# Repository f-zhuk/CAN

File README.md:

# CAN
## General description
The work is in progress and is currently not ready for real-life application.  
This repository contains hardware, firmware, and software dedicated to the creation of custom CANopen systems for vehicles.  
Such custom systems could fit old cars with heavily damaged harnesses and vehicles that do not have electronic equipment by default, for example, boats, kayaks, and bicycles.
## Hardware
The complete system should consist of multiple functional blocks. Blocks should be as cheap and simple as possible while implementing complete functions like combination switch assembly, left tail light assembly, and door controls.  
Each functional block should be designed around a unified MCU module and simple interconnection boards to adapt signals from the MCU module to the systems of the block.  
Interconnection boards may provide 24LC I2C EEPROM memory for identification and non-volatile parameter storage.  
### MCU
MCU module should be self-sufficient and electrically ready for insertion in the CAN bus system. To achieve this, the MCU module has a power supply converter and CAN driver aside from the controller.  
For the first prototype, the PIC18 family was selected. PIC18F83K26 has a built-in CAN periphery and a reasonable price.  
MCU module has +12V power input, +5V power input/output, CAN, UART, 8xGPIO(PC7:PC0)  
### USB-UART
Most important interconnection board. It provides a USB to UART bridge to provide a simple debug interface.  
USB-UART board is built with MCP2200. It is connected not only through UART but also 5xGPIO. Additionally, 24LC16 I2C EEPROM memory is connected to C6 and C7. C5 is connected to the bus termination control.  
## Firmware
Heavily updated code described in AN945. The application note code was written for an older MCU. PIC18F83K26AN945 is not supported by the compiler the code was written for and the code is not compatible with the new compiler.  
AN945 default config:  
ADC is on (probably unused)  
PORT D is all output (probably unused)  
PORT B pin 5 is bit 0 of TPDO1, pin 4 is bit 1  
State of PORTB pins 4 and 5 compared to their states on previous DemoProcessEvents() call, change, rise and fall events detected and distinguished, written to OD  
Dictionary object 0x6005subondex 1 (uIOinIntEnable) bits 0 and 1  
Async transmission for TPDO1 by default  
PDO transmission type could be changed by writing to TPDO1 subindex 2  
## Software
The software is written in Python.

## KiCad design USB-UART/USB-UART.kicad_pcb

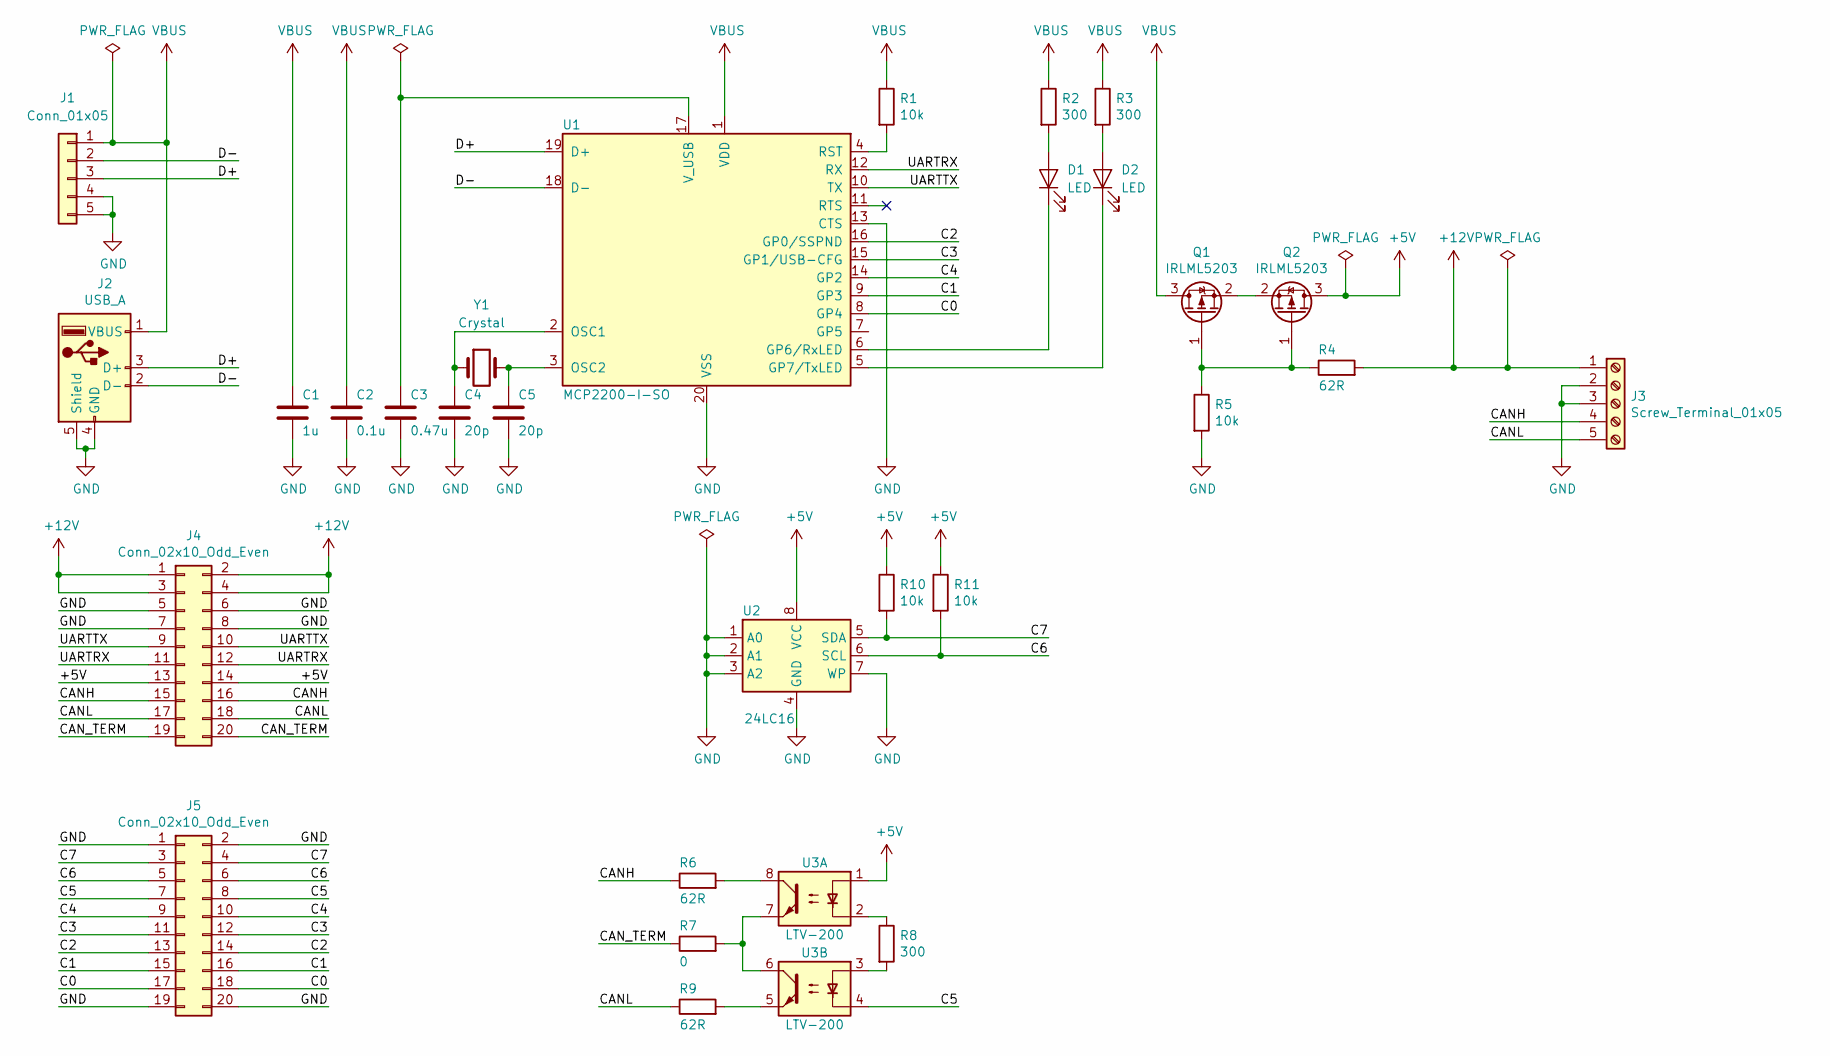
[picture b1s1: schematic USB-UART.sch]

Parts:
C1: 1u; C_0603_1608Metric
C2: 0.1u; C_0603_1608Metric
C3: 0.47u; C_0603_1608Metric
C4, C5: 20p; C_0603_1608Metric
D1, D2: LED; LED_0603_1608Metric
J1: Conn_01x05; PinHeader_1x05_P2.54mm_Vertical
J2: USB_A; USB_A_Integrated
J3: Screw_Terminal_01x05; TerminalBlock_bornier-5_P5.08mm
J4, J5: Conn_02x10_Odd_Even; PinSocket_2x10_P2.54mm_Vertical
Q1, Q2: IRLML5203; SOT-23
R1, R5, R10, R11: 10k; R_0603_1608Metric
R2, R3, R8: 300; R_0603_1608Metric
R4, R6, R9: 62R; R_0603_1608Metric
R7: 0; R_0603_1608Metric
U1: MCP2200-I-SO; SOIC-20W_7.5x12.8mm_P1.27mm
U2: 24LC16; SOIC-8_3.9x4.9mm_P1.27mm
U3: LTV-200; SOIC-8_3.9x4.9mm_P1.27mm
Y1: Crystal; Crystal_HC49-U_Vertical

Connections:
+5V: J4.13, J4.14, Q2.3 (D), R10.1, R11.1, U2.8 (VCC), U3.1
+12V: J3.1, J4.1, J4.2, J4.3, J4.4, R4.2
/C0: J5.17, J5.18, U1.8 (GP4)
/C1: J5.15, J5.16, U1.9 (GP3)
/C2: J5.13, J5.14, U1.16 (GP0/SSPND)
/C3: J5.11, J5.12, U1.15 (GP1/USB-CFG)
/C4: J5.9, J5.10, U1.14 (GP2)
/C5: J5.7, J5.8, U3.4
/C6: J5.5, J5.6, R11.2, U2.6 (SCL)
/C7: J5.3, J5.4, R10.2, U2.5 (SDA)
/CANH: J3.4, J4.15, J4.16, R6.1
/CANL: J3.5, J4.17, J4.18, R9.1
/CAN_TERM: J4.19, J4.20, R7.1
/D+: J1.3, J2.3 (D+), U1.19 (D+)
/D-: J1.2, J2.2 (D-), U1.18 (D-)
/UARTRX: J4.11, J4.12, U1.12 (RX)
/UARTTX: J4.9, J4.10, U1.10 (TX)
GND: C1.2, C2.2, C3.2, C4.2, C5.2, J1.4, J1.5, J2.4 (GND), J2.5 (Shield), J3.2, J3.3, J4.5, J4.6, J4.7, J4.8, J5.1, J5.2, J5.19, J5.20, R5.2, U1.13 (CTS), U1.20 (VSS), U2.1 (A0), U2.2 (A1), U2.3 (A2), U2.4 (GND), U2.7 (WP)
unnamed: C3.1, U1.17 (V_USB)
unnamed: C4.1, U1.2 (OSC1), Y1.1
unnamed: C5.1, U1.3 (OSC2), Y1.2
unnamed: D1.1 (K), U1.6 (GP6/RxLED)
unnamed: D1.2 (A), R2.2
unnamed: D2.1 (K), U1.5 (GP7/TxLED)
unnamed: D2.2 (A), R3.2
unnamed: Q1.1 (G), Q2.1 (G), R4.1, R5.1
unnamed: Q1.2 (S), Q2.2 (S)
unnamed: R1.2, U1.4 (RST)
unnamed: R6.2, U3.8
unnamed: R7.2, U3.6, U3.7
unnamed: R8.1, U3.2
unnamed: R8.2, U3.3
unnamed: R9.2, U3.5
VBUS: C1.1, C2.1, J1.1, J2.1 (VBUS), Q1.3 (D), R1.1, R2.1, R3.1, U1.1 (VDD)

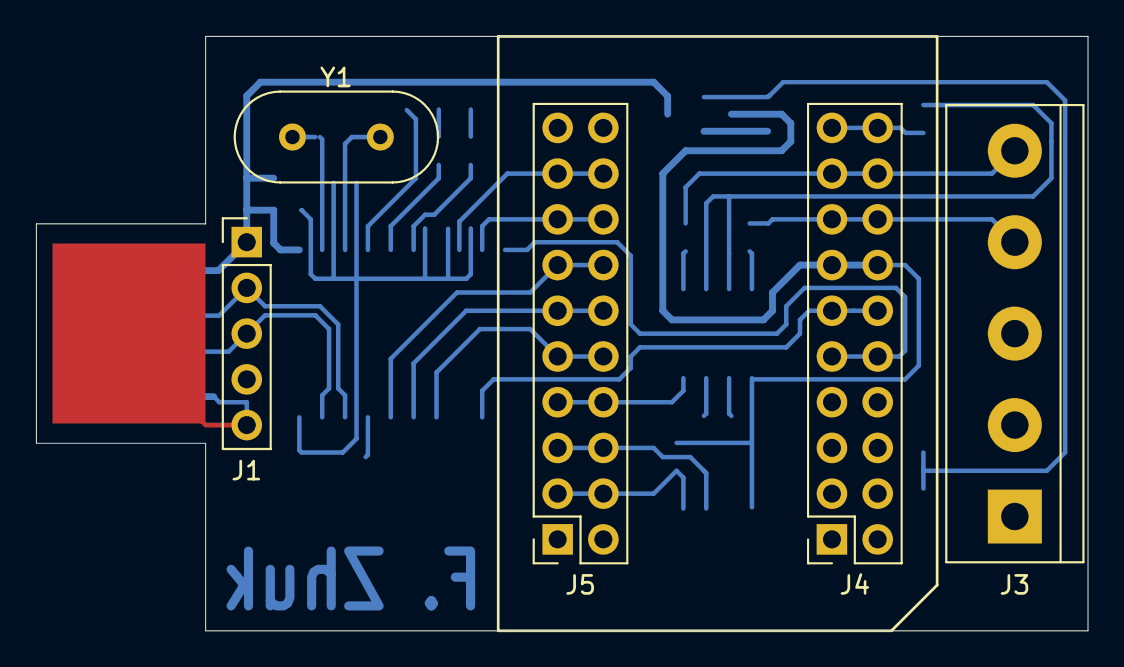
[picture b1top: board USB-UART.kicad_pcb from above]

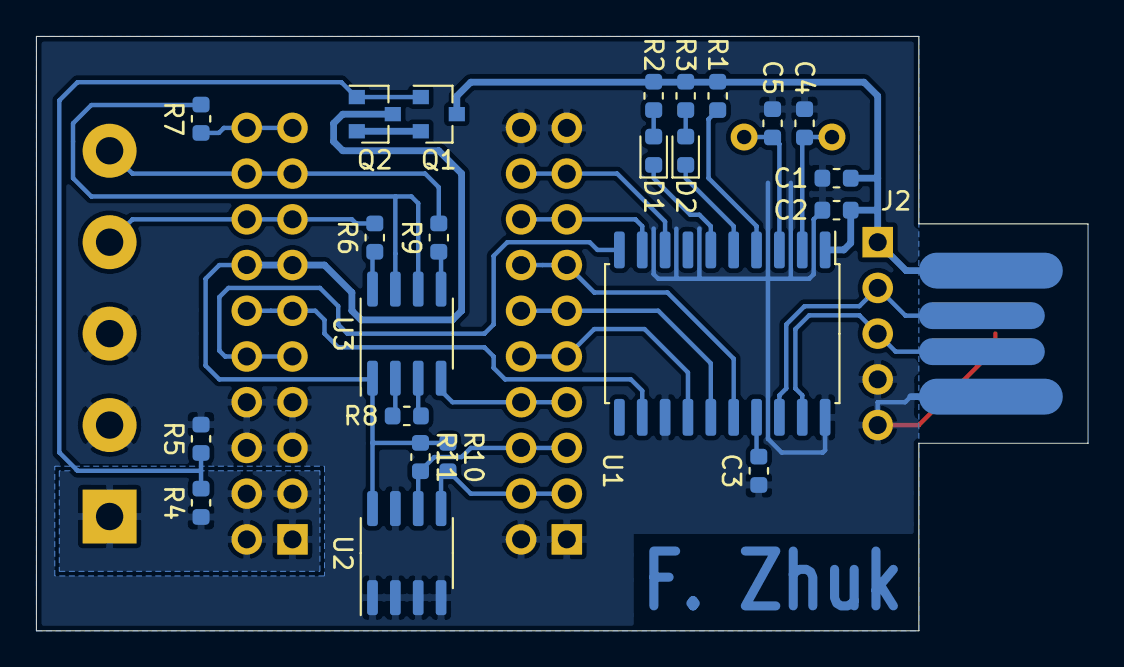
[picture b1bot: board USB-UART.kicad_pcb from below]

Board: 2 copper layers, 58.4 x 33.0 mm, 29 parts (24 on the bottom side), 34 nets.

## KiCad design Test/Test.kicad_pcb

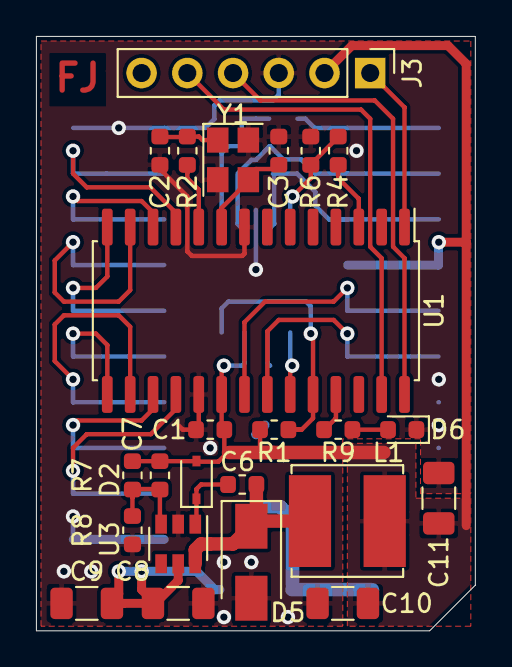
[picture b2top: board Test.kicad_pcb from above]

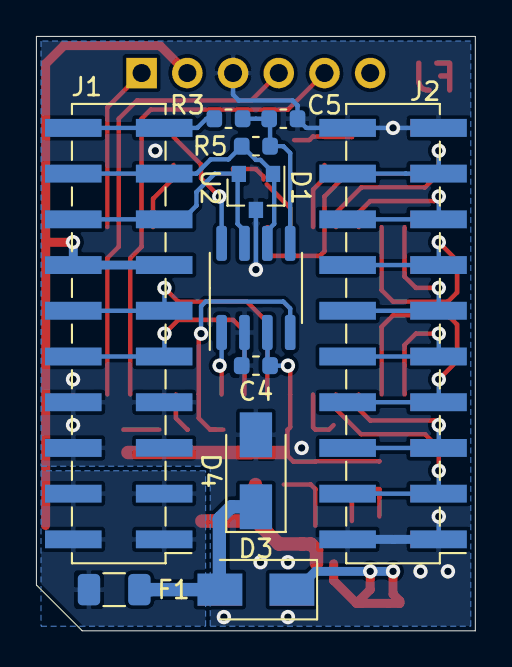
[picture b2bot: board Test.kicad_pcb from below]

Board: 4 copper layers, 24.4 x 33.0 mm, 35 parts (11 on the bottom side), 34 nets.

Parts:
C1, C4, C5, C6: 0.1u; C_0603_1608Metric
C2, C3, C7: 20p; C_0603_1608Metric
C8, C9, C10, C11: 10u; C_1206_3216Metric
D1: D_TVS_x2_AAC; SOT-23
D2: 1N4148WS; D_SOD-323
D3, D5: D_Schottky; D_SMA
D4: D_Zener; D_SMA
D6: LED; LED_0603_1608Metric
F1: Polyfuse; Fuse_1206_3216Metric
J1, J2: Conn_02x10_Odd_Even; PinHeader_2x10_P2.54mm_Vertical_SMD
J3: Conn_01x06; PinHeader_1x06_P2.54mm_Vertical
L1: 15u; L_Bourns_SRN6045TA
R1, R6: 47k; R_0603_1608Metric
R2, R4: 0; R_0603_1608Metric
R3, R5: 60; R_0603_1608Metric
R7: 52.3k; R_0603_1608Metric
R8: 10k; R_0603_1608Metric
R9: 300; R_0603_1608Metric
U1: PIC18F25K83-xSO; SOIC-28W_7.5x17.9mm_P1.27mm
U2: MCP2551-I-SN; SOIC-8_3.9x4.9mm_P1.27mm
U3: MCP16331CH; SOT-23-6
Y1: Crystal_GND24; Crystal_SMD_3225-4Pin_3.2x2.5mm

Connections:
+5V: C1.1, C4.1, C7.1, C10.1, C11.1, D2.2, J1.13, J1.14, J3.2, L1.1, R1.1, R7.1, U1.20, U2.3
+12V: F1.1, J1.1, J1.2, J1.3, J1.4
/C0: J2.17, J2.18, U1.11
/C1: J2.15, J2.16, U1.12
/C2: J2.13, J2.14, U1.13
/C3: J2.11, J2.12, U1.14
/C4: J2.9, J2.10, U1.15
/C5: J2.7, J2.8, U1.16
/C6: J2.5, J2.6, U1.17
/C7: J2.3, J2.4, U1.18
/CANH: D1.2, J1.15, J1.16, U2.7
/CANH_TERM: J1.19, J1.20, R3.1
/CANL: D1.1, J1.17, J1.18, R5.2, U2.6
/CANRX: R1.2, U1.24, U2.4
/CANSTB: R4.1, U1.3
/CANTX: U1.23, U2.1
/ICSPCLK: J3.5, U1.27
/ICSPDAT: J3.4, U1.28
/LED: R9.1, U1.25
/UARTRX: J1.9, J1.10, U1.22
/UARTTX: J1.11, J1.12, U1.21
/~MCLR: J3.1, U1.1
GND: C1.2, C2.2, C3.2, C4.2, C5.2, C8.2, C9.2, C10.2, C11.2, D1.3, D4.2, D5.2, D6.1, J1.5, J1.6, J1.7, J1.8, J2.1, J2.2, J2.19, J2.20, J3.3, R6.2, R8.2, U1.8, U1.19, U2.2, U3.2, Y1.2, Y1.4
unnamed: C2.1, R2.1, Y1.1
unnamed: C3.1, U1.9, Y1.3
unnamed: C5.1, R3.2, R5.1, U2.5
unnamed: C6.1, D2.1, U3.1
unnamed: C6.2, D5.1, L1.2, U3.6
unnamed: C7.2, R7.2, R8.1, U3.3
unnamed: C8.1, C9.1, D3.1, U3.5
unnamed: D3.2, D4.1, F1.2
unnamed: D6.2, R9.2
unnamed: R2.2, U1.10
unnamed: R4.2, R6.1, U2.8

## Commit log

2023-12-16 Initial HW upload
2023-12-16 Auto update
2023-12-16 Photo added
2023-12-16 Python desktop app added
2023-12-17 Firmware added
2025-11-23 Starting addition of a send feature
2025-11-23 Added send button callback
2026-01-14 Transmit capability added
2026-01-15 Fixed DLC value (trimmed to 4 bits)
2026-01-16 CAN bus message injection function added
2026-01-17 Implemented interrupt-based uart
2026-01-17 Fixed CANCDC CAN operation mode
2026-01-17 Switched both CANMCU and CANCDC projects to 125k baud rate
2026-01-17 SDO Transmit recognition added
2026-01-21 Started eds recognition
2026-02-12 PDO value display added, loop wait lowered
